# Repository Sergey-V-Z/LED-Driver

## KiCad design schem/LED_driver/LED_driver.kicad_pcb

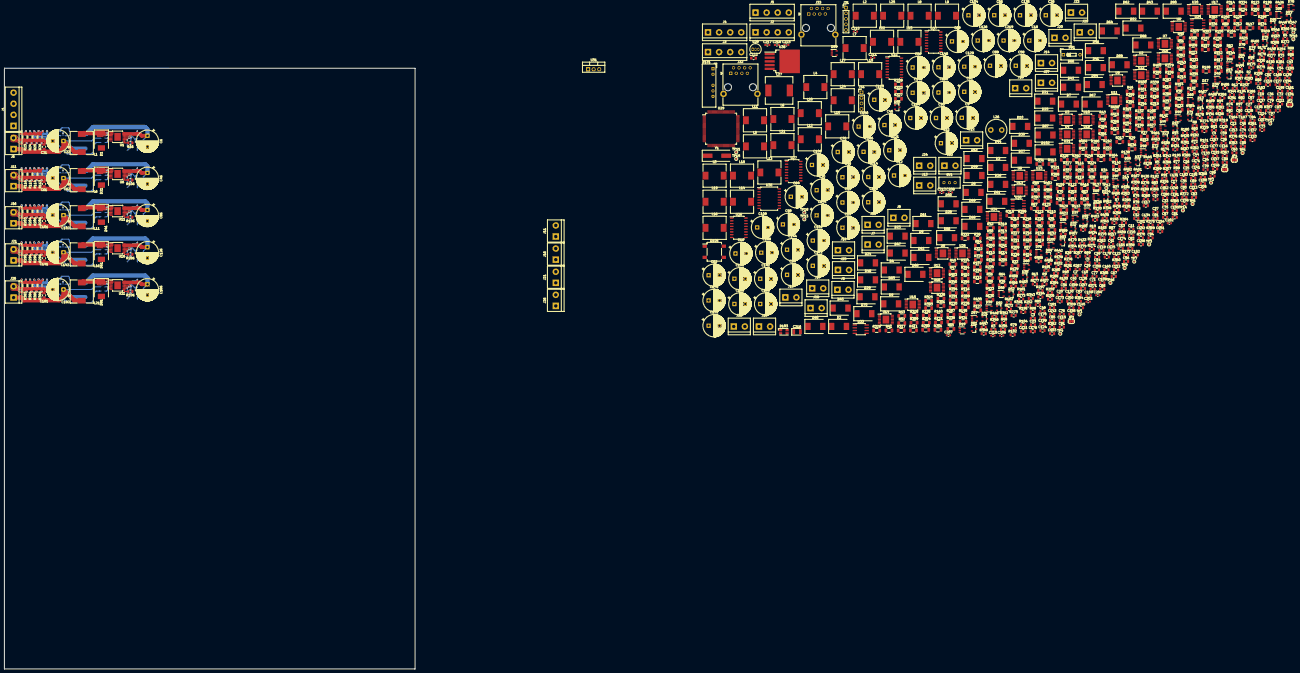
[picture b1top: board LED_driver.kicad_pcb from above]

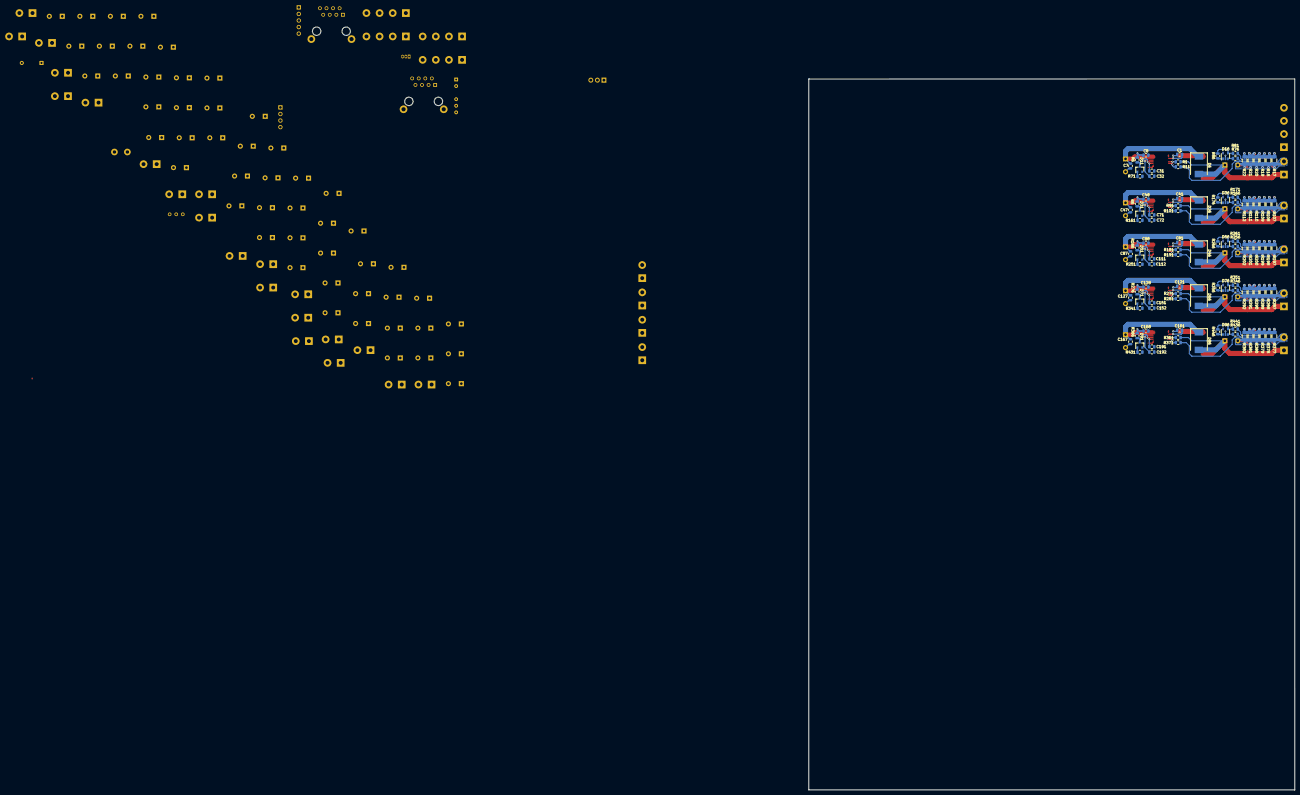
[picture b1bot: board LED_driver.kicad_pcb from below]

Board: 2 copper layers, 188.0 x 275.0 mm, 1054 parts (105 on the bottom side), 457 nets.

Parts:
C1, C2, C3, C4, C5, C7, C8, C10, C11, C13, C14, C16, C17, C19, C20, C21, C23, C25, C27, C29, C31, C33, C35, C37, C39, C41, C41#2, C42, C43, C44, C45, C47, C47#2, C48, C48#2, C50, C51, C53, C54, C56, C57, C59, C60, C61, C61#2, C63, C65, C67, C69, C71, C71#2, C73, C75, C77, C79, C81, C81#2, C82, C83, C84, C85, C87, C87#2, C88, C88#2, C90, C91, C93, C94, C96, C97, C99, C100, C101, C101#2, C103, C105, C107, C109, C111, C111#2, C113, C115, C117, C119, C121, C121#2, C122, C123, C124, C125, C127, C127#2, C128, C128#2, C130, C131, C133, C134, C136, C137, C139, C140, C141, C141#2, C143, C145, C147, C149, C151, C151#2, C153, C155, C157, C159, C161, C161#2, C162, C163, C164, C165, C167, C167#2, C168, C168#2, C170, C171, C173, C174, C176, C177, C179, C180, C181, C181#2, C183, C185, C187, C189, C191, C191#2, C193, C195, C197, C199, C201, C209, C213, C220: 0.1mkF; C_0805_2012Metric
C6, C9, C12, C15, C18, C22, C24, C26, C28, C30, C46, C46#2, C49, C52, C55, C58, C62, C62#2, C64, C66, C68, C70, C86, C86#2, C89, C92, C95, C98, C102, C102#2, C104, C106, C108, C110, C126, C126#2, C129, C132, C135, C138, C142, C142#2, C144, C146, C148, C150, C166, C166#2, C169, C172, C175, C178, C182, C182#2, C184, C186, C188, C190: 470mkF; CP_Radial_D10.0mm_P5.00mm
C32, C34, C36, C38, C40, C72, C72#2, C74, C76, C78, C80, C112, C112#2, C114, C116, C118, C120, C152, C152#2, C154, C156, C158, C160, C192, C192#2, C194, C196, C198, C200: 1mkF; C_0805_2012Metric
C202, C203, C204, C205, C206, C207, C208, C212, C215: 0.1uf; C_0603_1608Metric
C210, C211: 18pF; C_0603_1608Metric
C214: 100uf 16v; CP_Radial_D10.0mm_P5.00mm
C216: 10uf 10v; CP_EIA-3528-21_Kemet-B
C217, C218, C223: 0.1 mkf; C_0603_1608Metric_Pad1.05x0.95mm_HandSolder
C219: 220uf 50v; CP_Radial_D10.0mm_P5.00mm
C221: 470uf 50v; CP_Radial_D10.0mm_P5.00mm
C222: 10 mkf; C_0805_2012Metric_Pad1.15x1.40mm_HandSolder
D1, D2, D3, D4, D5, D6, D7, D8, D9, D10, D21, D21#2, D22, D23, D24, D25, D26, D26#2, D27, D28, D29, D30, D41, D41#2, D42, D43, D44, D45, D46, D46#2, D47, D48, D49, D50, D61, D61#2, D62, D63, D64, D65, D66, D66#2, D67, D68, D69, D70, D81, D81#2, D82, D83, D84, D85, D86, D86#2, D87, D88, D89, D90, D102: D_Schottky; D_SMC
D11, D12, D13, D14, D15, D31, D31#2, D32, D33, D34, D35, D51, D51#2, D52, D53, D54, D55, D71, D71#2, D72, D73, D74, D75, D91, D91#2, D92, D93, D94, D95: Si2300; SOT-23
D16, D17, D18, D19, D20, D36, D36#2, D37, D38, D39, D40, D56, D56#2, D57, D58, D59, D60, D76, D76#2, D77, D78, D79, D80, D96, D96#2, D97, D98, D99, D100: lmc7101; SOT-23-5
D101: AM1DS-0505S-NZ; Converter_DCDC_muRata_NMAxxxxSC_THT
D103: Led_RGB_CA_2; LED_Avago_PLCC4_3.2x2.8mm_CW
D104: SM712; SOT-23
D105: B380R; Diode_Bridge_Vishay_DFS
D106: LED; LED_0805_2012Metric
J1, J2, J3, J4, J5: Screw_Terminal_01x04; TerminalBlock_bornier-4_P5.08mm
J6, J7, J8, J9, J10, J11, J11#2, J12, J13, J14, J15, J16, J16#2, J17, J18, J19, J20, J21, J21#2, J22, J23, J24, J25, J26, J26#2, J27, J28, J29, J30, J35: Screw_Terminal_01x02; TerminalBlock_bornier-2_P5.08mm
J31: SWD; PinHeader_1x05_P2.54mm_Vertical
J32, J33: RJ45_Shielded; RJ45_Ninigi_GE
J34: DEBUG; PinHeader_1x04_P2.54mm_Vertical
JP1: TX_UA; SolderJumper-2_P1.3mm_Bridged_RoundedPad1.0x1.5mm
JP2: RX_UA; SolderJumper-2_P1.3mm_Bridged_RoundedPad1.0x1.5mm
JP3: TX_CAN; SolderJumper-2_P1.3mm_Open_RoundedPad1.0x1.5mm
JP4: RX_CAN; SolderJumper-2_P1.3mm_Open_RoundedPad1.0x1.5mm
L1, L2, L3, L4, L5, L6, L6#2, L7, L8, L9, L10, L11, L11#2, L12, L13, L14, L15, L16, L16#2, L17, L18, L19, L20, L21, L21#2, L22, L23, L24, L25: 22mkH; L_10.4x10.4_H4.8
L26: 22 uH; L_Radial_D9.5mm_P5.00mm_Fastron_07HVP
L27: 33 uH; L_12x12mm_H8mm
R1, R2, R3, R4, R5, R11, R12, R13, R14, R15, R76, R77, R78, R79, R80, R81, R82, R83, R84, R85, R91, R91#2, R92, R93, R94, R95, R101, R101#2, R102, R103, R104, R105, R166, R166#2, R167, R168, R169, R170, R171, R171#2, R172, R173, R174, R175, R181, R181#2, R182, R183, R184, R185, R191, R191#2, R192, R193, R194, R195, R256, R256#2, R257, R258, R259, R260, R261, R261#2, R262, R263, R264, R265, R271, R271#2, R272, R273, R274, R275, R281, R281#2, R282, R283, R284, R285, R346, R346#2, R347, R348, R349, R350, R351, R351#2, R352, R353, R354, R355, R361, R361#2, R362, R363, R364, R365, R371, R371#2, R372, R373, R374, R375, R436, R436#2, R437, R438, R439, R440, R441, R441#2, R442, R443, R444, R445, R455, R465: 1K; R_0805_2012Metric
R6, R6#2, R7, R8, R9, R10, R71, R72, R73, R74, R75, R96, R97, R98, R99, R100, R161, R161#2, R162, R163, R164, R165, R186, R186#2, R187, R188, R189, R190, R251, R251#2, R252, R253, R254, R255, R276, R276#2, R277, R278, R279, R280, R341, R341#2, R342, R343, R344, R345, R366, R366#2, R367, R368, R369, R370, R431, R431#2, R432, R433, R434, R435: 100K; R_0805_2012Metric
R16, R27, R38, R49, R60, R106, R106#2, R117, R128, R139, R150, R196, R196#2, R207, R218, R229, R240, R286, R286#2, R297, R308, R319, R330, R376, R376#2, R387, R398, R409, R420, R457: 100; R_0805_2012Metric
R17, R18, R19, R20, R21, R22, R23, R24, R25, R26, R28, R29, R30, R31, R32, R33, R34, R35, R36, R37, R39, R40, R41, R42, R43, R44, R45, R46, R47, R48, R50, R51, R52, R53, R54, R55, R56, R57, R58, R59, R61, R62, R63, R64, R65, R66, R67, R68, R69, R70, R107, R107#2, R108, R108#2, R109, R109#2, R110, R110#2, R111, R111#2, R112, R112#2, R113, R113#2, R114, R114#2, R115, R115#2, R116, R116#2, R118, R119, R120, R121, R122, R123, R124, R125, R126, R127, R129, R130, R131, R132, R133, R134, R135, R136, R137, R138, R140, R141, R142, R143, R144, R145, R146, R147, R148, R149, R151, R152, R153, R154, R155, R156, R157, R158, R159, R160, R197, R197#2, R198, R198#2, R199, R199#2, R200, R200#2, R201, R201#2, R202, R202#2, R203, R203#2, R204, R204#2, R205, R205#2, R206, R206#2, R208, R209, R210, R211, R212, R213, R214, R215, R216, R217, R219, R220, R221, R222, R223, R224, R225, R226, R227, R228, R230, R231, R232, R233, R234, R235, R236, R237, R238, R239, R241, R242, R243, R244, R245, R246, R247, R248, R249, R250, R287, R287#2, R288, R288#2, R289, R289#2, R290, R290#2, R291, R291#2, R292, R292#2, R293, R293#2, R294, R294#2, R295, R295#2, R296, R296#2, R298, R299, R300, R301, R302, R303, R304, R305, R306, R307, R309, R310, R311, R312, R313, R314, R315, R316, R317, R318, R320, R321, R322, R323, R324, R325, R326, R327, R328, R329, R331, R332, R333, R334, R335, R336, R337, R338, R339, R340, R377, R377#2, R378, R378#2, R379, R379#2, R380, R380#2, R381, R381#2, R382, R382#2, R383, R383#2, R384, R384#2, R385, R385#2, R386, R386#2, R388, R389, R390, R391, R392, R393, R394, R395, R396, R397, R399, R400, R401, R402, R403, R404, R405, R406, R407, R408, R410, R411, R412, R413, R414, R415, R416, R417, R418, R419, R421, R422, R423, R424, R425, R426, R427, R428, R429, R430: 1R; R_1206_3216Metric
R86, R87, R88, R89, R90, R176, R176#2, R177, R178, R179, R180, R266, R266#2, R267, R268, R269, R270, R356, R356#2, R357, R358, R359, R360, R446, R446#2, R447, R448, R449, R450, R451, R453: 10K; R_0805_2012Metric
R452: 510; R_0805_2012Metric
R454: 15; R_1206_3216Metric
R456: 3K; R_0805_2012Metric
R458, R460, R464, R469: 10k; R_0805_2012Metric_Pad1.15x1.40mm_HandSolder
R459: 120 Om; R_0805_2012Metric_Pad1.15x1.40mm_HandSolder
R461, R463: 10; R_0805_2012Metric_Pad1.15x1.40mm_HandSolder
R462: 3.3k; R_0805_2012Metric_Pad1.15x1.40mm_HandSolder
R466: 1.5k; R_0805_2012Metric_Pad1.15x1.40mm_HandSolder
R467: 1k; R_0805_2012Metric_Pad1.15x1.40mm_HandSolder
R468: 750 Om; R_0805_2012Metric_Pad1.15x1.40mm_HandSolder
RV1: 10k; Potentiometer_Bourns_3296W_Vertical
SW1: SW_DIP_x01; SW_DIP_SPSTx01_Slide_9.78x4.72mm_W7.62mm_P2.54mm
TP1: A8; TestPoint_Pad_D1.0mm
TP2: REF; TestPoint_Pad_D1.0mm
TP3: F6; TestPoint_Pad_D1.0mm
TP4: B0; TestPoint_Pad_D1.0mm
TP5: E1; TestPoint_Pad_D1.0mm
TP6: B1; TestPoint_Pad_D1.0mm
TP7: B2; TestPoint_Pad_D1.0mm
TP8: E6; TestPoint_Pad_D1.0mm
TP9: GND; TestPoint_Pad_D1.0mm
TP10: E7; TestPoint_Pad_D1.0mm
TP11: E10; TestPoint_Pad_D1.0mm
TP12: E12; TestPoint_Pad_D1.0mm
TP13: B13; TestPoint_Pad_D1.0mm
TP14: C4; TestPoint_Pad_D1.0mm
TP15: C5; TestPoint_Pad_D1.0mm
TP16: C13; TestPoint_Pad_D1.0mm
TP17: C14; TestPoint_Pad_D1.0mm
TP18: C15; TestPoint_Pad_D1.0mm
U1, U2, U3, U4, U5, U6, U6#2, U7, U8, U9, U10, U11, U11#2, U12, U13, U14, U15, U16, U16#2, U17, U18, U19, U20, U21, U21#2, U22, U23, U24, U25: LM3406; TSSOP-14-1EP_4.4x5mm_P0.65mm
U26, U27, U32, U37: 74HC595; SOP-16_4.55x10.3mm_P1.27mm
U28: TL431LP; TO-92_Inline
U29: STM32F303VCTx; LQFP-100_14x14mm_P0.5mm
U30: MCP2551-I_SN; SO-8_3.9x4.9mm_P1.27mm
U31: LM1117-3.3; TO-220-3_Vertical
U33: GD25Q16C; PowerIntegrations_SO-8
U34: MAX3485; SOIC-8_3.9x4.9mm_P1.27mm
U35: ISO7341C; SOIC-16W_7.5x10.3mm_P1.27mm
U36: LM2596S-ADJ; TO-263-5_TabPin3
Y1: Crystal_Small; Crystal_SMD_HC49-SD

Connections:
+3V3: C201.1, C202.1, C203.1, C204.1, C205.1, C206.1, C207.1, C209.1, C212.2, C213.1, C215.1, C216.1, C217.2, C220.1, D16.2, D17.2, D18.2, D19.2, D20.2, D36.2, D36#2.2, D37.2, D38.2, D39.2, D40.2, D56.2, D56#2.2, D57.2, D58.2, D59.2, D60.2, D76.2, D76#2.2, D77.2, D78.2, D79.2, D80.2, D96.2, D96#2.2, D97.2, D98.2, D99.2, D100.2, D103.4, J34.4, R451.2, R453.2, R469.1, U26.16, U27.16, U29.6, U29.22, U29.28, U29.50, U29.75, U29.100, U31.2, U32.16, U33.8, U35.1, U35.7, U37.16
/+5v_IN_ISO: C218.1, C222.1, C223.1, J32.4, J33.4, R460.2, U30.3, U34.8, U35.10, U35.16
/A_ISO: J32.2, J33.2, R459.1, R463.2
/B_ISO: J32.1, J33.1, R461.2, SW1.2
/DE: U29.71, U35.4
/DE_ISO: R464.2, U34.2, U34.3, U35.13
/DIM_CH1: R16.2, R106.2, R196.2, R286.2, R376.2, U29.84
/DIM_CH2: R106#2.2, U29.85
/DIM_CH3: R196#2.2, U29.92
/DIM_CH4: R286#2.2, U29.93
/DIM_CH5: R376#2.2, U29.95
/DIM_CH6: R27.2, U29.1
/DIM_CH7: R117.2, U29.2
/DIM_CH8: R207.2, U29.3
/DIM_CH9: R297.2, U29.4
/DIM_CH10: R387.2, U29.10
/DIM_CH11: R38.2, U29.11
/DIM_CH12: R128.2, U29.31
/DIM_CH13: R218.2, U29.32
/DIM_CH14: R308.2, U29.40
/DIM_CH15: R398.2, U29.42
/DIM_CH16: R49.2, U29.44
/DIM_CH17: R139.2, U29.47
/DIM_CH18: R229.2, U29.48
/DIM_CH19: R319.2, U29.62
/DIM_CH20: R409.2, U29.63
/DIM_CH21: R60.2, U29.64
/DIM_CH22: R150.2, U29.65
/DIM_CH23: R240.2, U29.66
/DIM_CH24: R330.2, R420.2, U29.70
/GND_5v_IN_ISO: C218.2, C222.2, C223.2, D104.3, J32.3, J32.SH, J33.3, J33.SH, R458.1, R464.1, U30.2, U34.5, U35.9, U35.15
/IN_+24v: C221.1, D105.1, J32.7, J33.7, U36.1
/IN_GND_24v: C219.2, C221.2, D101.2, D102.2, D105.3, J32.8, J33.8, R465.1, U36.3, U36.5
/Isens_CH1: D16.1, D36.1, D56.1, D76.1, D96.1, R86.2, R176.2, R266.2, R356.2, R446.2, U29.15
/Isens_CH2: D36#2.1, R176#2.2, U29.16
/Isens_CH3: D56#2.1, R266#2.2, U29.17
/Isens_CH4: D76#2.1, R356#2.2, U29.18
/Isens_CH5: D96#2.1, R446#2.2, U29.19
/Isens_CH6: D17.1, R87.2, U29.23
/Isens_CH7: D37.1, R177.2, U29.24
/Isens_CH8: D57.1, R267.2, U29.25
/Isens_CH9: D77.1, R357.2, U29.26
/Isens_CH10: D97.1, R447.2, U29.27
/Isens_CH11: D18.1, R88.2, U29.29
/Isens_CH12: D38.1, R178.2, U29.30
/Isens_CH13: D58.1, R268.2, U29.39
/Isens_CH14: D78.1, R358.2, U29.45
/Isens_CH15: D98.1, R448.2, U29.46
/Isens_CH16: D19.1, R89.2, U29.51
/Isens_CH17: D39.1, R179.2, U29.53
/Isens_CH18: D59.1, R269.2, U29.54
/Isens_CH19: D79.1, R359.2, U29.55
/Isens_CH20: D99.1, R449.2, U29.56
/Isens_CH21: D20.1, R90.2, U29.57
/Isens_CH22: D40.1, R180.2, U29.58
/Isens_CH23: D60.1, R270.2, U29.59
/Isens_CH24: D80.1, R360.2, U29.60
/Isens_CH25: D100.1, R450.2, U29.61
/LED_S1: R468.1, U37.3
/LED_S2: R467.1, U37.2
/LED_S3: R466.1, U37.1
/OFF_CH1: D11.1, D31.1, D51.1, D71.1, D91.1, R71.2, R161.2, R251.2, R341.2, R431.2, U26.15
/OFF_CH2: D31#2.1, R161#2.2, U26.1
/OFF_CH3: D51#2.1, R251#2.2, U26.2
/OFF_CH4: D71#2.1, R341#2.2, U26.3
/OFF_CH5: D91#2.1, R431#2.2, U26.4
/OFF_CH6: D12.1, R72.2, U26.5
/OFF_CH7: D32.1, R162.2, U26.6
/OFF_CH8: D52.1, R252.2, U26.7
/OFF_CH9: D72.1, R342.2, U27.15
/OFF_CH10: D92.1, R432.2, U27.1
/OFF_CH11: D13.1, R73.2, U27.2
/OFF_CH12: D33.1, R163.2, U27.3
/OFF_CH13: D53.1, R253.2, U27.4
/OFF_CH14: D73.1, R343.2, U27.5
/OFF_CH15: D93.1, R433.2, U27.6
/OFF_CH16: D14.1, R74.2, U27.7
/OFF_CH17: D34.1, R164.2, U32.15
/OFF_CH18: D54.1, R254.2, U32.1
/OFF_CH19: D74.1, R344.2, U32.2
/OFF_CH20: D94.1, R434.2, U32.3
/OFF_CH21: D15.1, R75.2, U32.4
/OFF_CH22: D35.1, R165.2, U32.5
/OFF_CH23: D55.1, R255.2, U32.6
/OFF_CH24: D75.1, R345.2, U32.7
/OFF_CH25: D95.1, R435.2, U37.15
/RESET: C208.2, J31.1, R453.1, U29.14
/RX: JP2.2, JP4.1, U35.6
/RX_ISO: R460.1, U30.4, U34.1, U35.11
/SPI3_CLK: U29.78, U33.6
/SPI3_CS: U29.83, U33.1
/SPI3_HOLD: U29.96, U33.7
/SPI3_MISO: U29.79, U33.2
/SPI3_MOSI: U29.80, U33.5
/SPI3_WP: U29.97, U33.3
/SWDCL: J31.4, U29.76
/SWDIO: J31.2, U29.72
/TX: JP1.2, JP3.1, U35.5
/TX_ISO: U30.1, U34.4, U35.12
/USART2_RX: J34.3, U29.87
/USART2_TX: J34.1, U29.86
/spi_CS: U26.12, U27.12, U29.77, U32.12, U37.12
/spi_MOSI: U26.14, U29.91
/spi_SCK: U26.11, U27.11, U29.89, U32.11, U37.11
/~MR: U26.10, U27.10, U29.90, U32.10, U37.10
/~OE: U26.13, U27.13, U29.88, U32.13, U37.13
GND: C6.2, C7.2, C8.2, C9.2, C10.2, C11.2, C12.2, C13.2, C14.2, C15.2, C16.2, C17.2, C18.2, C19.2, C20.2, C31.2, C32.2, C33.2, C34.2, C35.2, C36.2, C37.2, C38.2, C39.2, C40.2, C46.2, C46#2.2, C47.2, C47#2.2, C48.2, C48#2.2, C49.2, C50.2, C51.2, C52.2, C53.2, C54.2, C55.2, C56.2, C57.2, C58.2, C59.2, C60.2, C71.2, C71#2.2, C72.2, C72#2.2, C73.2, C74.2, C75.2, C76.2, C77.2, C78.2, C79.2, C80.2, C86.2, C86#2.2, C87.2, C87#2.2, C88.2, C88#2.2, C89.2, C90.2, C91.2, C92.2, C93.2, C94.2, C95.2, C96.2, C97.2, C98.2, C99.2, C100.2, C111.2, C111#2.2, C112.2, C112#2.2, C113.2, C114.2, C115.2, C116.2, C117.2, C118.2, C119.2, C120.2, C126.2, C126#2.2, C127.2, C127#2.2, C128.2, C128#2.2, C129.2, C130.2, C131.2, C132.2, C133.2, C134.2, C135.2, C136.2, C137.2, C138.2, C139.2, C140.2, C151.2, C151#2.2, C152.2, C152#2.2, C153.2, C154.2, C155.2, C156.2, C157.2, C158.2, C159.2, C160.2, C166.2, C166#2.2, C167.2, C167#2.2, C168.2, C168#2.2, C169.2, C170.2, C171.2, C172.2, C173.2, C174.2, C175.2, C176.2, C177.2, C178.2, C179.2, C180.2, C191.2, C191#2.2, C192.2, C192#2.2, C193.2, C194.2, C195.2, C196.2, C197.2, C198.2, C199.2, C200.2, C201.2, C202.2, C203.2, C204.2, C205.2, C206.2, C207.2, C208.1, C209.2, C210.2, C211.1, C212.1, C213.2, C214.2, C215.2, C216.2, C217.1, C220.2, D1.2, D2.2, D3.2, D4.2, D5.2, D11.2, D12.2, D13.2, D14.2, D15.2, D16.5, D17.5, D18.5, D19.5, D20.5, D21.2, D21#2.2, D22.2, D23.2, D24.2, D25.2, D31.2, D31#2.2, D32.2, D33.2, D34.2, D35.2, D36.5, D36#2.5, D37.5, D38.5, D39.5, D40.5, D41.2, D41#2.2, D42.2, D43.2, D44.2, D45.2, D51.2, D51#2.2, D52.2, D53.2, D54.2, D55.2, D56.5, D56#2.5, D57.5, D58.5, D59.5, D60.5, D61.2, D61#2.2, D62.2, D63.2, D64.2, D65.2, D71.2, D71#2.2, D72.2, D73.2, D74.2, D75.2, D76.5, D76#2.5, D77.5, D78.5, D79.5, D80.5, D81.2, D81#2.2, D82.2, D83.2, D84.2, D85.2, D91.2, D91#2.2, D92.2, D93.2, D94.2, D95.2, D96.5, D96#2.5, D97.5, D98.5, D99.5, D100.5, D101.4, D106.1, J1.1, J1.2, J2.1, J2.2, J3.1, J3.2, J4.1, J4.2, J5.1, J5.2, J31.3, J34.2, R17.1, R18.1, R19.1, R20.1, R21.1, R22.1, R23.1, R24.1, R25.1, R26.1, R28.1, R29.1, R30.1, R31.1, R32.1, R33.1, R34.1, R35.1, R36.1, R37.1, R39.1, R40.1, R41.1, R42.1, R43.1, R44.1, R45.1, R46.1, R47.1, R48.1, R50.1, R51.1, R52.1, R53.1, R54.1, R55.1, R56.1, R57.1, R58.1, R59.1, R61.1, R62.1, R63.1, R64.1, R65.1, R66.1, R67.1, R68.1, R69.1, R70.1, R71.1, R72.1, R73.1, R74.1, R75.1, R81.1, R82.1, R83.1, R84.1, R85.1, R107.1, R107#2.1, R108.1, R108#2.1, R109.1, R109#2.1, R110.1, R110#2.1, R111.1, R111#2.1, R112.1, R112#2.1, R113.1, R113#2.1, R114.1, R114#2.1, R115.1, R115#2.1, R116.1, R116#2.1, R118.1, R119.1, R120.1, R121.1, R122.1, R123.1, R124.1, R125.1, R126.1, R127.1, R129.1, R130.1, R131.1, R132.1, R133.1, R134.1, R135.1, R136.1, R137.1, R138.1, R140.1, R141.1, R142.1, R143.1, R144.1, R145.1, R146.1, R147.1, R148.1, R149.1, R151.1, R152.1, R153.1, R154.1, R155.1, R156.1, R157.1, R158.1, R159.1, R160.1, R161.1, R161#2.1, R162.1, R163.1, R164.1, R165.1, R171.1, R171#2.1, R172.1, R173.1, R174.1, R175.1, R197.1, R197#2.1, R198.1, R198#2.1, R199.1, R199#2.1, R200.1, R200#2.1, R201.1, R201#2.1, R202.1, R202#2.1, R203.1, R203#2.1, R204.1, R204#2.1, R205.1, R205#2.1, R206.1, R206#2.1, R208.1, R209.1, R210.1, R211.1, R212.1, R213.1, R214.1, R215.1, R216.1, R217.1, R219.1, R220.1, R221.1, R222.1, R223.1, R224.1, R225.1, R226.1, R227.1, R228.1, R230.1, R231.1, R232.1, R233.1, R234.1, R235.1, R236.1, R237.1, R238.1, R239.1, R241.1, R242.1, R243.1, R244.1, R245.1, R246.1, R247.1, R248.1, R249.1, R250.1, R251.1, R251#2.1, R252.1, R253.1, R254.1, R255.1, R261.1, R261#2.1, R262.1, R263.1, R264.1, R265.1, R287.1, R287#2.1, R288.1, R288#2.1, R289.1, R289#2.1, R290.1, R290#2.1, R291.1, R291#2.1, R292.1, R292#2.1, R293.1, R293#2.1, R294.1, R294#2.1, R295.1, R295#2.1, R296.1, R296#2.1, R298.1, R299.1, R300.1, R301.1, R302.1, R303.1, R304.1, R305.1, R306.1, R307.1, R309.1, R310.1, R311.1, R312.1, R313.1, R314.1, R315.1, R316.1, R317.1, R318.1, R320.1, R321.1, R322.1, R323.1, R324.1, R325.1, R326.1, R327.1, R328.1, R329.1, R331.1, R332.1, R333.1, R334.1, R335.1, R336.1, R337.1, R338.1, R339.1, R340.1, R341.1, R341#2.1, R342.1, R343.1, R344.1, R345.1, R351.1, R351#2.1, R352.1, R353.1, R354.1, R355.1, R377.1, R377#2.1, R378.1, R378#2.1, R379.1, R379#2.1, R380.1, R380#2.1, R381.1, R381#2.1, R382.1, R382#2.1, R383.1, R383#2.1, R384.1, R384#2.1, R385.1, R385#2.1, R386.1, R386#2.1, R388.1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
unnamed: C1.1, C41.1, C81.1, C121.1, C161.1, D1.1, D21.1, D41.1, D61.1, D81.1, L1.1, L6.1, L11.1, L16.1, L21.1, U1.1, U1.2, U6.1, U6.2, U11.1, U11.2, U16.1, U16.2, U21.1, U21.2
unnamed: C1.2, C41.2, C81.2, C121.2, C161.2, U1.3, U6.3, U11.3, U16.3, U21.3
unnamed: C2.1, D2.1, L2.1, U2.1, U2.2
unnamed: C2.2, U2.3
unnamed: C3.1, D3.1, L3.1, U3.1, U3.2
unnamed: C3.2, U3.3
unnamed: C4.1, D4.1, L4.1, U4.1, U4.2
unnamed: C4.2, U4.3
unnamed: C5.1, D5.1, L5.1, U5.1, U5.2
unnamed: C5.2, U5.3
unnamed: C9.1, C10.1, C11.1, C49.1, C50.1, C51.1, C89.1, C90.1, C91.1, C129.1, C130.1, C131.1, C169.1, C170.1, C171.1, D7.1, D27.1, D47.1, D67.1, D87.1, J2.3, J2.4, R7.2, R97.2, R187.2, R277.2, R367.2, U2.12, U2.13, U2.14, U7.12, U7.13, U7.14, U12.12, U12.13, U12.14, U17.12, U17.13, U17.14, U22.12, U22.13, U22.14
unnamed: C12.1, C13.1, C14.1, C52.1, C53.1, C54.1, C92.1, C93.1, C94.1, C132.1, C133.1, C134.1, C172.1, C173.1, C174.1, D8.1, D28.1, D48.1, D68.1, D88.1, J3.3, J3.4, R8.2, R98.2, R188.2, R278.2, R368.2, U3.12, U3.13, U3.14, U8.12, U8.13, U8.14, U13.12, U13.13, U13.14, U18.12, U18.13, U18.14, U23.12, U23.13, U23.14
unnamed: C21.1, C22.1, C61.1, C62.1, C101.1, C102.1, C141.1, C142.1, C181.1, C182.1, D6.2, D26.2, D46.2, D66.2, D86.2, J6.1, J11.1, J16.1, J21.1, J26.1, L1.2, L6.2, L11.2, L16.2, L21.2, R1.1, R91.1, R181.1, R271.1, R361.1
unnamed: C21.2, C22.2, C61.2, C62.2, C101.2, C102.2, C141.2, C142.2, C181.2, C182.2, J6.2, J11.2, J16.2, J21.2, J26.2, R11.1, R17.2, R18.2, R19.2, R20.2, R21.2, R22.2, R23.2, R24.2, R25.2, R26.2, R76.1, R101.1, R107.2, R108.2, R109.2, R110.2, R111.2, R112.2, R113.2, R114.2, R115.2, R116.2, R166.1, R191.1, R197.2, R198.2, R199.2, R200.2, R201.2, R202.2, R203.2, R204.2, R205.2, R206.2, R256.1, R281.1, R287.2, R288.2, R289.2, R290.2, R291.2, R292.2, R293.2, R294.2, R295.2, R296.2, R346.1, R371.1, R377.2, R378.2, R379.2, R380.2, R381.2, R382.2, R383.2, R384.2, R385.2, R386.2, R436.1
unnamed: C23.1, C24.1, D7.2, J7.1, L2.2, R2.1
unnamed: C23.2, C24.2, J7.2, R12.1, R28.2, R29.2, R30.2, R31.2, R32.2, R33.2, R34.2, R35.2, R36.2, R37.2, R77.1
unnamed: C25.1, C26.1, D8.2, J8.1, L3.2, R3.1
unnamed: C25.2, C26.2, J8.2, R13.1, R39.2, R40.2, R41.2, R42.2, R43.2, R44.2, R45.2, R46.2, R47.2, R48.2, R78.1
unnamed: C27.1, C28.1, D9.2, J9.1, L4.2, R4.1
unnamed: C27.2, C28.2, J9.2, R14.1, R50.2, R51.2, R52.2, R53.2, R54.2, R55.2, R56.2, R57.2, R58.2, R59.2, R79.1
unnamed: C29.1, C30.1, D10.2, J10.1, L5.2, R5.1
unnamed: C29.2, C30.2, J10.2, R15.1, R61.2, R62.2, R63.2, R64.2, R65.2, R66.2, R67.2, R68.2, R69.2, R70.2, R80.1
unnamed: C31.1, C71.1, C111.1, C151.1, C191.1, U1.9, U6.9, U11.9, U16.9, U21.9
unnamed: C32.1, C72.1, C112.1, C152.1, C192.1, U1.11, U6.11, U11.11, U16.11, U21.11
unnamed: C33.1, U2.9
unnamed: C34.1, U2.11
unnamed: C35.1, U3.9
unnamed: C36.1, U3.11
unnamed: C37.1, U4.9
unnamed: C38.1, U4.11
unnamed: C39.1, U5.9
unnamed: C40.1, U5.11
unnamed: C41#2.1, D21#2.1, L6#2.1, U6#2.1, U6#2.2
unnamed: C41#2.2, U6#2.3
unnamed: C42.1, D22.1, L7.1, U7.1, U7.2
unnamed: C42.2, U7.3
unnamed: C43.1, D23.1, L8.1, U8.1, U8.2
unnamed: C43.2, U8.3
unnamed: C44.1, D24.1, L9.1, U9.1, U9.2
unnamed: C44.2, U9.3
unnamed: C45.1, D25.1, L10.1, U10.1, U10.2
unnamed: C45.2, U10.3
unnamed: C61#2.1, C62#2.1, D26#2.2, J11#2.1, L6#2.2, R91#2.1
unnamed: C61#2.2, C62#2.2, J11#2.2, R101#2.1, R107#2.2, R108#2.2, R109#2.2, R110#2.2, R111#2.2, R112#2.2, R113#2.2, R114#2.2, R115#2.2, R116#2.2, R166#2.1
unnamed: C63.1, C64.1, D27.2, J12.1, L7.2, R92.1
unnamed: C63.2, C64.2, J12.2, R102.1, R118.2, R119.2, R120.2, R121.2, R122.2, R123.2, R124.2, R125.2, R126.2, R127.2, R167.1
unnamed: C65.1, C66.1, D28.2, J13.1, L8.2, R93.1
unnamed: C65.2, C66.2, J13.2, R103.1, R129.2, R130.2, R131.2, R132.2, R133.2, R134.2, R135.2, R136.2, R137.2, R138.2, R168.1
unnamed: C67.1, C68.1, D29.2, J14.1, L9.2, R94.1
unnamed: C67.2, C68.2, J14.2, R104.1, R140.2, R141.2, R142.2, R143.2, R144.2, R145.2, R146.2, R147.2, R148.2, R149.2, R169.1
unnamed: C69.1, C70.1, D30.2, J15.1, L10.2, R95.1
unnamed: C69.2, C70.2, J15.2, R105.1, R151.2, R152.2, R153.2, R154.2, R155.2, R156.2, R157.2, R158.2, R159.2, R160.2, R170.1
unnamed: C71#2.1, U6#2.9
unnamed: C72#2.1, U6#2.11
unnamed: C73.1, U7.9
unnamed: C74.1, U7.11
unnamed: C75.1, U8.9
unnamed: C76.1, U8.11
unnamed: C77.1, U9.9
unnamed: C78.1, U9.11
unnamed: C79.1, U10.9
unnamed: C80.1, U10.11
unnamed: C81#2.1, D41#2.1, L11#2.1, U11#2.1, U11#2.2
unnamed: C81#2.2, U11#2.3
unnamed: C82.1, D42.1, L12.1, U12.1, U12.2
unnamed: C82.2, U12.3
unnamed: C83.1, D43.1, L13.1, U13.1, U13.2
unnamed: C83.2, U13.3
unnamed: C84.1, D44.1, L14.1, U14.1, U14.2
unnamed: C84.2, U14.3
unnamed: C85.1, D45.1, L15.1, U15.1, U15.2
unnamed: C85.2, U15.3
unnamed: C18.1, C19.1, C20.1, C58.1, C59.1, C60.1, C98.1, C99.1, C100.1, C138.1, C139.1, C140.1, C178.1, C179.1, C180.1, D10.1, D30.1, D50.1, D70.1, D90.1, J5.3, J5.4, R10.2, R100.2, R190.2, R280.2, R370.2, U5.12, U5.13, U5.14, U10.12, U10.13, U10.14, U15.12, U15.13, U15.14, U20.12, U20.13, U20.14, U25.12, U25.13, U25.14
unnamed: C101#2.1, C102#2.1, D46#2.2, J16#2.1, L11#2.2, R181#2.1
unnamed: C101#2.2, C102#2.2, J16#2.2, R191#2.1, R197#2.2, R198#2.2, R199#2.2, R200#2.2, R201#2.2, R202#2.2, R203#2.2, R204#2.2, R205#2.2, R206#2.2, R256#2.1
unnamed: C103.1, C104.1, D47.2, J17.1, L12.2, R182.1
unnamed: C103.2, C104.2, J17.2, R192.1, R208.2, R209.2, R210.2, R211.2, R212.2, R213.2, R214.2, R215.2, R216.2, R217.2, R257.1
unnamed: C105.1, C106.1, D48.2, J18.1, L13.2, R183.1
unnamed: C105.2, C106.2, J18.2, R193.1, R219.2, R220.2, R221.2, R222.2, R223.2, R224.2, R225.2, R226.2, R227.2, R228.2, R258.1
unnamed: C107.1, C108.1, D49.2, J19.1, L14.2, R184.1
unnamed: C107.2, C108.2, J19.2, R194.1, R230.2, R231.2, R232.2, R233.2, R234.2, R235.2, R236.2, R237.2, R238.2, R239.2, R259.1
unnamed: C109.1, C110.1, D50.2, J20.1, L15.2, R185.1
unnamed: C109.2, C110.2, J20.2, R195.1, R241.2, R242.2, R243.2, R244.2, R245.2, R246.2, R247.2, R248.2, R249.2, R250.2, R260.1
unnamed: C111#2.1, U11#2.9
unnamed: C112#2.1, U11#2.11
unnamed: C113.1, U12.9
unnamed: C114.1, U12.11
unnamed: C115.1, U13.9
unnamed: C116.1, U13.11
unnamed: C117.1, U14.9
unnamed: C118.1, U14.11
unnamed: C119.1, U15.9
unnamed: C120.1, U15.11
unnamed: C121#2.1, D61#2.1, L16#2.1, U16#2.1, U16#2.2
unnamed: C121#2.2, U16#2.3
unnamed: C122.1, D62.1, L17.1, U17.1, U17.2
unnamed: C122.2, U17.3
unnamed: C123.1, D63.1, L18.1, U18.1, U18.2
unnamed: C123.2, U18.3
unnamed: C124.1, D64.1, L19.1, U19.1, U19.2
unnamed: C124.2, U19.3
unnamed: C125.1, D65.1, L20.1, U20.1, U20.2
unnamed: C125.2, U20.3
unnamed: C6.1, C7.1, C8.1, C46.1, C46#2.1, C47.1, C47#2.1, C48.1, C48#2.1, C86.1, C86#2.1, C87.1, C87#2.1, C88.1, C88#2.1, C126.1, C126#2.1, C127.1, C127#2.1, C128.1, C128#2.1, C166.1, C166#2.1, C167.1, C167#2.1, C168.1, C168#2.1, D6.1, D26.1, D26#2.1, D46.1, D46#2.1, D66.1, D66#2.1, D86.1, D86#2.1, J1.3, J1.4, R6.2, R6#2.2, R96.2, R186.2, R186#2.2, R276.2, R276#2.2, R366.2, R366#2.2, U1.12, U1.13, U1.14, U6.12, U6.13, U6.14, U6#2.12, U6#2.13, U6#2.14, U11.12, U11.13, U11.14, U11#2.12, U11#2.13, U11#2.14, U16.12, U16.13, U16.14, U16#2.12, U16#2.13, U16#2.14, U21.12, U21.13, U21.14, U21#2.12, U21#2.13, U21#2.14
unnamed: C15.1, C16.1, C17.1, C55.1, C56.1, C57.1, C95.1, C96.1, C97.1, C135.1, C136.1, C137.1, C175.1, C176.1, C177.1, D9.1, D29.1, D49.1, D69.1, D89.1, J4.3, J4.4, R9.2, R99.2, R189.2, R279.2, R369.2, U4.12, U4.13, U4.14, U9.12, U9.13, U9.14, U14.12, U14.13, U14.14, U19.12, U19.13, U19.14, U24.12, U24.13, U24.14
unnamed: C141#2.1, C142#2.1, D66#2.2, J21#2.1, L16#2.2, R271#2.1
unnamed: C141#2.2, C142#2.2, J21#2.2, R281#2.1, R287#2.2, R288#2.2, R289#2.2, R290#2.2, R291#2.2, R292#2.2, R293#2.2, R294#2.2, R295#2.2, R296#2.2, R346#2.1
unnamed: C143.1, C144.1, D67.2, J22.1, L17.2, R272.1
unnamed: C143.2, C144.2, J22.2, R282.1, R298.2, R299.2, R300.2, R301.2, R302.2, R303.2, R304.2, R305.2, R306.2, R307.2, R347.1
unnamed: C145.1, C146.1, D68.2, J23.1, L18.2, R273.1
unnamed: C145.2, C146.2, J23.2, R283.1, R309.2, R310.2, R311.2, R312.2, R313.2, R314.2, R315.2, R316.2, R317.2, R318.2, R348.1
unnamed: C147.1, C148.1, D69.2, J24.1, L19.2, R274.1
unnamed: C147.2, C148.2, J24.2, R284.1, R320.2, R321.2, R322.2, R323.2, R324.2, R325.2, R326.2, R327.2, R328.2, R329.2, R349.1
unnamed: C149.1, C150.1, D70.2, J25.1, L20.2, R275.1
unnamed: C149.2, C150.2, J25.2, R285.1, R331.2, R332.2, R333.2, R334.2, R335.2, R336.2, R337.2, R338.2, R339.2, R340.2, R350.1
unnamed: C151#2.1, U16#2.9
unnamed: C152#2.1, U16#2.11
unnamed: C153.1, U17.9
unnamed: C154.1, U17.11
unnamed: C155.1, U18.9
unnamed: C156.1, U18.11
unnamed: C157.1, U19.9
unnamed: C158.1, U19.11
unnamed: C159.1, U20.9
unnamed: C160.1, U20.11
unnamed: C161#2.1, D81#2.1, L21#2.1, U21#2.1, U21#2.2
unnamed: C161#2.2, U21#2.3
unnamed: C162.1, D82.1, L22.1, U22.1, U22.2
unnamed: C162.2, U22.3
unnamed: C163.1, D83.1, L23.1, U23.1, U23.2
unnamed: C163.2, U23.3
unnamed: C164.1, D84.1, L24.1, U24.1, U24.2
unnamed: C164.2, U24.3
unnamed: C165.1, D85.1, L25.1, U25.1, U25.2
unnamed: C165.2, U25.3
unnamed: C181#2.1, C182#2.1, D86#2.2, J26#2.1, L21#2.2, R361#2.1
unnamed: C181#2.2, C182#2.2, J26#2.2, R371#2.1, R377#2.2, R378#2.2, R379#2.2, R380#2.2, R381#2.2, R382#2.2, R383#2.2, R384#2.2, R385#2.2, R386#2.2, R436#2.1
unnamed: C183.1, C184.1, D87.2, J27.1, L22.2, R362.1
unnamed: C183.2, C184.2, J27.2, R372.1, R388.2, R389.2, R390.2, R391.2, R392.2, R393.2, R394.2, R395.2, R396.2, R397.2, R437.1
unnamed: C185.1, C186.1, D88.2, J28.1, L23.2, R363.1
unnamed: C185.2, C186.2, J28.2, R373.1, R399.2, R400.2, R401.2, R402.2, R403.2, R404.2, R405.2, R406.2, R407.2, R408.2, R438.1
unnamed: C187.1, C188.1, D89.2, J29.1, L24.2, R364.1
unnamed: C187.2, C188.2, J29.2, R374.1, R410.2, R411.2, R412.2, R413.2, R414.2, R415.2, R416.2, R417.2, R418.2, R419.2, R439.1
unnamed: C189.1, C190.1, D90.2, J30.1, L25.2, R365.1
unnamed: C189.2, C190.2, J30.2, R375.1, R421.2, R422.2, R423.2, R424.2, R425.2, R426.2, R427.2, R428.2, R429.2, R430.2, R440.1
unnamed: C191#2.1, U21#2.9
unnamed: C192#2.1, U21#2.11
unnamed: C193.1, U22.9
unnamed: C194.1, U22.11
unnamed: C195.1, U23.9
unnamed: C196.1, U23.11
unnamed: C197.1, U24.9
unnamed: C198.1, U24.11
unnamed: C199.1, U25.9
unnamed: C200.1, U25.11
unnamed: C210.1, U29.12, Y1.1
unnamed: C211.2, U29.13, Y1.2
unnamed: C214.1, L26.2, R454.2, U31.3
unnamed: C219.1, D101.1, L27.2, R462.2
unnamed: D11.3, D31.3, D51.3, D71.3, D91.3, R6.1, R6#2.1, R186.1, R276.1, R366.1, U1.10, U6.10, U11.10, U16.10, U21.10
unnamed: D12.3, R7.1, U2.10
unnamed: D13.3, R8.1, U3.10
unnamed: D14.3, R9.1, U4.10
unnamed: D15.3, R10.1, U5.10
unnamed: D16.3, D36.3, D56.3, D76.3, D96.3, R76.2, R166.2, R256.2, R346.2, R436.2
unnamed: D16.4, D36.4, D56.4, D76.4, D96.4, R81.2, R86.1, R171.2, R176.1, R261.2, R266.1, R351.2, R356.1, R441.2, R446.1
unnamed: D17.3, R77.2
unnamed: D17.4, R82.2, R87.1
unnamed: D18.3, R78.2
unnamed: D18.4, R83.2, R88.1
unnamed: D19.3, R79.2
unnamed: D19.4, R84.2, R89.1
unnamed: D20.3, R80.2
unnamed: D20.4, R85.2, R90.1
unnamed: D31#2.3, R96.1, U6#2.10
unnamed: D32.3, R97.1, U7.10
unnamed: D33.3, R98.1, U8.10
unnamed: D34.3, R99.1, U9.10
unnamed: D35.3, R100.1, U10.10
unnamed: D36#2.3, R166#2.2
unnamed: D36#2.4, R171#2.2, R176#2.1
unnamed: D37.3, R167.2
unnamed: D37.4, R172.2, R177.1
unnamed: D38.3, R168.2
unnamed: D38.4, R173.2, R178.1
unnamed: D39.3, R169.2
unnamed: D39.4, R174.2, R179.1
unnamed: D40.3, R170.2
unnamed: D40.4, R175.2, R180.1
unnamed: D51#2.3, R186#2.1, U11#2.10
unnamed: D52.3, R187.1, U12.10
unnamed: D53.3, R188.1, U13.10
unnamed: D54.3, R189.1, U14.10
unnamed: D55.3, R190.1, U15.10
unnamed: D56#2.3, R256#2.2
unnamed: D56#2.4, R261#2.2, R266#2.1
unnamed: D57.3, R257.2
unnamed: D57.4, R262.2, R267.1
unnamed: D58.3, R258.2
unnamed: D58.4, R263.2, R268.1
unnamed: D59.3, R259.2
unnamed: D59.4, R264.2, R269.1
unnamed: D60.3, R260.2
unnamed: D60.4, R265.2, R270.1
unnamed: D71#2.3, R276#2.1, U16#2.10
unnamed: D72.3, R277.1, U17.10
unnamed: D73.3, R278.1, U18.10
unnamed: D74.3, R279.1, U19.10
unnamed: D75.3, R280.1, U20.10
unnamed: D76#2.3, R346#2.2
unnamed: D76#2.4, R351#2.2, R356#2.1
unnamed: D77.3, R347.2
unnamed: D77.4, R352.2, R357.1
unnamed: D78.3, R348.2
unnamed: D78.4, R353.2, R358.1
unnamed: D79.3, R349.2
unnamed: D79.4, R354.2, R359.1
unnamed: D80.3, R350.2
unnamed: D80.4, R355.2, R360.1
unnamed: D91#2.3, R366#2.1, U21#2.10
unnamed: D92.3, R367.1, U22.10
unnamed: D93.3, R368.1, U23.10
unnamed: D94.3, R369.1, U24.10
unnamed: D95.3, R370.1, U25.10
unnamed: D96#2.3, R436#2.2
unnamed: D96#2.4, R441#2.2, R446#2.1
unnamed: D97.3, R437.2
unnamed: D97.4, R442.2, R447.1
unnamed: D98.3, R438.2
unnamed: D98.4, R443.2, R448.1
unnamed: D99.3, R439.2
unnamed: D99.4, R444.2, R449.1
unnamed: D100.3, R440.2
unnamed: D100.4, R445.2, R450.1
unnamed: D101.6, L26.1
unnamed: D102.1, L27.1, U36.2
unnamed: D103.1, R466.2
unnamed: D103.2, R467.2
unnamed: D103.3, R468.2
unnamed: D104.1, R463.1, U30.6, U34.6
unnamed: D104.2, R461.1, U30.7, U34.7
unnamed: D105.2, J35.1
unnamed: D105.4, J35.2
unnamed: D106.2, R469.2
unnamed: JP1.1, U29.68
unnamed: JP2.1, U29.69
unnamed: JP3.2, U29.81
unnamed: JP4.2, U29.82
unnamed: R1.2, R91.2, R181.2, R271.2, R361.2, U1.5, U6.5, U11.5, U16.5, U21.5
unnamed: R2.2, U2.5
unnamed: R3.2, U3.5
unnamed: R4.2, U4.5
unnamed: R5.2, U5.5
unnamed: R11.2, R101.2, R191.2, R281.2, R371.2, U1.6, U6.6, U11.6, U16.6, U21.6
unnamed: R12.2, U2.6
unnamed: R13.2, U3.6
unnamed: R14.2, U4.6
unnamed: R15.2, U5.6
unnamed: R16.1, R106.1, R196.1, R286.1, R376.1, U1.8, U6.8, U11.8, U16.8, U21.8
unnamed: R27.1, U2.8
unnamed: R38.1, U3.8
unnamed: R49.1, U4.8
unnamed: R60.1, U5.8
unnamed: R91#2.2, U6#2.5
unnamed: R92.2, U7.5
unnamed: R93.2, U8.5
unnamed: R94.2, U9.5
unnamed: R95.2, U10.5
unnamed: R101#2.2, U6#2.6
unnamed: R102.2, U7.6
unnamed: R103.2, U8.6
unnamed: R104.2, U9.6
unnamed: R105.2, U10.6
unnamed: R106#2.1, U6#2.8
unnamed: R117.1, U7.8
unnamed: R128.1, U8.8
unnamed: R139.1, U9.8
unnamed: R150.1, U10.8
unnamed: R181#2.2, U11#2.5
unnamed: R182.2, U12.5
unnamed: R183.2, U13.5
unnamed: R184.2, U14.5
unnamed: R185.2, U15.5
unnamed: R191#2.2, U11#2.6
unnamed: R192.2, U12.6
unnamed: R193.2, U13.6
unnamed: R194.2, U14.6
unnamed: R195.2, U15.6
unnamed: R196#2.1, U11#2.8
unnamed: R207.1, U12.8
unnamed: R218.1, U13.8
unnamed: R229.1, U14.8
unnamed: R240.1, U15.8
unnamed: R271#2.2, U16#2.5
unnamed: R272.2, U17.5
unnamed: R273.2, U18.5
unnamed: R274.2, U19.5
unnamed: R275.2, U20.5
unnamed: R281#2.2, U16#2.6
unnamed: R282.2, U17.6
unnamed: R283.2, U18.6
unnamed: R284.2, U19.6
unnamed: R285.2, U20.6
unnamed: R286#2.1, U16#2.8
unnamed: R297.1, U17.8
unnamed: R308.1, U18.8
unnamed: R319.1, U19.8
unnamed: R330.1, U20.8
unnamed: R361#2.2, U21#2.5
unnamed: R362.2, U22.5
unnamed: R363.2, U23.5
unnamed: R364.2, U24.5
unnamed: R365.2, U25.5
unnamed: R371#2.2, U21#2.6
unnamed: R372.2, U22.6
unnamed: R373.2, U23.6
unnamed: R374.2, U24.6
unnamed: R375.2, U25.6
unnamed: R376#2.1, U21#2.8
unnamed: R387.1, U22.8
unnamed: R398.1, U23.8
unnamed: R409.1, U24.8
unnamed: R420.1, U25.8
unnamed: R451.1, R452.1, U29.94
unnamed: R454.1, R455.2, TP2.1, U28.3, U29.21
unnamed: R455.1, R456.2, RV1.1, RV1.2, U28.1
unnamed: R456.1, R457.2
unnamed: R458.2, U30.8
unnamed: R459.2, SW1.1
unnamed: R462.1, R465.2, U36.4
unnamed: TP1.1, U29.67
unnamed: TP3.1, U29.73
unnamed: TP4.1, U29.35
unnamed: TP5.1, U29.98
unnamed: TP6.1, U29.36
unnamed: TP7.1, U29.37
unnamed: TP8.1, U29.5
unnamed: TP10.1, U29.38
unnamed: TP11.1, U29.41
unnamed: TP12.1, U29.43
unnamed: TP13.1, U29.52
unnamed: TP14.1, U29.33
unnamed: TP15.1, U29.34
unnamed: TP16.1, U29.7
unnamed: TP17.1, U29.8
unnamed: TP18.1, U29.9
unnamed: U1.4, U6.4, U11.4, U16.4, U21.4
unnamed: U26.9, U27.14
unnamed: U27.9, U32.14
unnamed: U32.9, U37.14

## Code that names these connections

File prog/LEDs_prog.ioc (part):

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Mcu.Name=STM32F303V(B-C)Tx
Mcu.Package=LQFP100
Mcu.UserName=STM32F303VCTx
PA0.GPIOParameters=GPIO_Label
PA0.GPIO_Label=Isens_CH6
PA0.Mode=IN1-Single-Ended
PA0.Signal=ADC1_IN1
PA1.GPIOParameters=GPIO_Label
PA1.GPIO_Label=Isens_CH7
PA1.Mode=IN2-Single-Ended
PA1.Signal=ADC1_IN2
PA10.Mode=Asynchronous
PA10.Signal=USART1_RX
PA11.GPIOParameters=GPIO_Label
PA11.GPIO_Label=DIM_CH24
PA11.Signal=S_TIM1_CH4
PA12.Mode=Hardware Flow Control (RS485)
PA12.Signal=USART1_DE
PA13.Mode=Serial_Wire
PA13.Signal=SYS_JTMS-SWDIO
PA14.Mode=Serial_Wire
PA14.Signal=SYS_JTCK-SWCLK
PA15.Mode=NSS_Signal_Hard_Output
PA15.Signal=SPI1_NSS
PA2.GPIOParameters=GPIO_Label
PA2.GPIO_Label=Isens_CH8
PA2.Mode=IN3-Single-Ended
PA2.Signal=ADC1_IN3
PA3.GPIOParameters=GPIO_Label
PA3.GPIO_Label=Isens_CH9
PA3.Mode=IN4-Single-Ended
PA3.Signal=ADC1_IN4
PA4.GPIOParameters=GPIO_Label
PA4.GPIO_Label=Isens_CH11
PA4.Mode=IN1-Single-Ended
PA4.Signal=ADC2_IN1
PA5.GPIOParameters=GPIO_Label
PA5.GPIO_Label=Isens_CH12
PA5.Mode=IN2-Single-Ended
PA5.Signal=ADC2_IN2
PA6.GPIOParameters=GPIO_Label
PA6.GPIO_Label=DIM_CH12
PA6.Signal=S_TIM16_CH1
PA7.GPIOParameters=GPIO_Label
PA7.GPIO_Label=DIM_CH13
PA7.Signal=S_TIM17_CH1
PA9.Mode=Asynchronous
PA9.Signal=USART1_TX
PB10.GPIOParameters=GPIO_Label
PB10.GPIO_Label=DIM_CH17
PB10.Signal=S_TIM2_CH3
PB11.GPIOParameters=GPIO_Label
PB11.GPIO_Label=DIM_CH18
PB11.Signal=S_TIM2_CH4
PB12.GPIOParameters=GPIO_Label
PB12.GPIO_Label=Isens_CH16
PB12.Mode=IN3-Single-Ended
PB12.Signal=ADC4_IN3
PB14.GPIOParameters=GPIO_Label
PB14.GPIO_Label=Isens_CH17
PB14.Mode=IN4-Single-Ended
PB14.Signal=ADC4_IN4
PB15.GPIOParameters=GPIO_Label
PB15.GPIO_Label=Isens_CH18
PB15.Mode=IN5-Single-Ended
PB15.Signal=ADC4_IN5
PB3.Mode=TX_Only_Simplex_Unidirect_Master
PB3.Signal=SPI1_SCK
PB4.GPIOParameters=GPIO_Label
PB4.GPIO_Label=MR
PB4.Signal=GPIO_Output
PB5.Mode=TX_Only_Simplex_Unidirect_Master
PB5.Signal=SPI1_MOSI
PB6.GPIOParameters=GPIO_Label
PB6.GPIO_Label=DIM_CH3
PB6.Signal=S_TIM4_CH1
PB7.GPIOParameters=GPIO_Label
PB7.GPIO_Label=DIM_CH4
PB7.Signal=S_TIM4_CH2
PB8.GPIOParameters=GPIO_Label
PB8.GPIO_Label=DIM_CH5
PB8.Signal=S_TIM4_CH3
PB9.GPIOParameters=GPIO_Label
PB9.GPIO_Label=SPI3_HOLD
PB9.Signal=GPIO_Output
PC0.GPIOParameters=GPIO_Label
PC0.GPIO_Label=Isens_CH1
PC0.Signal=ADCx_IN6
PC1.GPIOParameters=GPIO_Label
PC1.GPIO_Label=Isens_CH2
PC1.Signal=ADCx_IN7
PC10.Mode=Full_Duplex_Master
PC10.Signal=SPI3_SCK
PC11.Mode=Full_Duplex_Master
PC11.Signal=SPI3_MISO
PC12.Mode=Full_Duplex_Master
PC12.Signal=SPI3_MOSI
PC2.GPIOParameters=GPIO_Label
PC2.GPIO_Label=Isens_CH3
PC2.Signal=ADCx_IN8
PC3.GPIOParameters=GPIO_Label
PC3.GPIO_Label=Isens_CH4
PC3.Signal=ADCx_IN9
PC6.GPIOParameters=GPIO_Label
PC6.GPIO_Label=DIM_CH20
PC6.Signal=S_TIM8_CH1
PC7.GPIOParameters=GPIO_Label
PC7.GPIO_Label=DIM_CH21
PC7.Signal=S_TIM8_CH2
PC8.GPIOParameters=GPIO_Label
PC8.GPIO_Label=DIM_CH22
PC8.Signal=S_TIM8_CH3
PC9.GPIOParameters=GPIO_Label
PC9.GPIO_Label=DIM_CH23
PC9.Signal=S_TIM8_CH4
PD0.Mode=Master
PD0.Signal=CAN_RX
PD1.Mode=Master
PD1.Signal=CAN_TX
PD10.GPIOParameters=GPIO_Label
PD10.GPIO_Label=Isens_CH21
PD10.Signal=ADCx_IN7P
PD11.GPIOParameters=GPIO_Label
PD11.GPIO_Label=Isens_CH22
PD11.Signal=ADCx_IN8P
PD12.GPIOParameters=GPIO_Label
PD12.GPIO_Label=Isens_CH23
PD12.Signal=ADCx_IN9P
PD13.GPIOParameters=GPIO_Label
PD13.GPIO_Label=Isens_CH24
PD13.Signal=ADCx_IN10P
PD14.GPIOParameters=GPIO_Label
PD14.GPIO_Label=Isens_CH25
PD14.Signal=ADCx_IN11
PD15.GPIOParameters=GPIO_Label
PD15.GPIO_Label=DIM_CH19
PD15.Signal=S_TIM4_CH4
PD2.GPIOParameters=GPIO_Label
PD2.GPIO_Label=SPI3_CS
PD2.Signal=GPIO_Output
PD3.GPIOParameters=GPIO_Label
PD3.GPIO_Label=DIM_CH1
PD3.Signal=S_TIM2_CH1_ETR
PD4.GPIOParameters=GPIO_Label
PD4.GPIO_Label=DIM_CH2
PD4.Signal=S_TIM2_CH2
PD5.Mode=Asynchronous
PD5.Signal=USART2_TX
PD6.Mode=Asynchronous
PD6.Signal=USART2_RX
PD7.GPIOParameters=GPIO_Label
PD7.GPIO_Label=OE
PD7.Signal=GPIO_Output
PD8.GPIOParameters=GPIO_Label
PD8.GPIO_Label=Isens_CH19
PD8.Mode=IN12-Single-Ended
PD8.Signal=ADC4_IN12
PD9.GPIOParameters=GPIO_Label
PD9.GPIO_Label=Isens_CH20
PD9.Mode=IN13-Single-Ended
PD9.Signal=ADC4_IN13
PE0.GPIOParameters=GPIO_Label
PE0.GPIO_Label=SPI3_WP
PE0.Signal=GPIO_Output
PE11.GPIOParameters=GPIO_Label
PE11.GPIO_Label=DIM_CH15
PE11.Signal=S_TIM1_CH2
PE13.GPIOParameters=GPIO_Label
PE13.GPIO_Label=DIM_CH16
PE13.Signal=S_TIM1_CH3
PE14.GPIOParameters=GPIO_Label
PE14.GPIO_Label=Isens_CH14
PE14.Mode=IN1-Single-Ended
PE14.Signal=ADC4_IN1
PE15.GPIOParameters=GPIO_Label
PE15.GPIO_Label=Isens_CH15
PE15.Mode=IN2-Single-Ended
PE15.Signal=ADC4_IN2
PE2.GPIOParameters=GPIO_Label
PE2.GPIO_Label=DIM_CH6
PE2.Signal=S_TIM3_CH1
PE3.GPIOParameters=GPIO_Label
PE3.GPIO_Label=DIM_CH7
PE3.Signal=S_TIM3_CH2
PE4.GPIOParameters=GPIO_Label
PE4.GPIO_Label=DIM_CH8
PE4.Signal=S_TIM3_CH3
PE5.GPIOParameters=GPIO_Label
PE5.GPIO_Label=DIM_CH9
PE5.Signal=S_TIM3_CH4
PE8.GPIOParameters=GPIO_Label
PE8.GPIO_Label=Isens_CH13
PE8.Signal=ADCx_IN6P
PE9.GPIOParameters=GPIO_Label
PE9.GPIO_Label=DIM_CH14
PE9.Signal=S_TIM1_CH1
PF0-OSC_IN.Mode=HSE-External-Oscillator
PF0-OSC_IN.Signal=RCC_OSC_IN
PF1-OSC_OUT.Mode=HSE-External-Oscillator
PF1-OSC_OUT.Signal=RCC_OSC_OUT
PF10.GPIOParameters=GPIO_Label
PF10.GPIO_Label=DIM_CH11
PF10.Signal=S_TIM15_CH2
PF2.GPIOParameters=GPIO_Label
PF2.GPIO_Label=Isens_CH5
PF2.Signal=ADCx_IN10
PF4.GPIOParameters=GPIO_Label
PF4.GPIO_Label=Isens_CH10
PF4.Mode=IN5-Single-Ended
PF4.Signal=ADC1_IN5
PF9.GPIOParameters=GPIO_Label
PF9.GPIO_Label=DIM_CH10
PF9.Signal=S_TIM15_CH1
RCC.HSEPLLFreq_Value=12000000
RCC.HSE_VALUE=12000000
RCC.SYSCLKFreq_VALUE=72000000
RCC.SYSCLKSourceVirtual=RCC_SYSCLKSOURCE_PLLCLK
board=custom

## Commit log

2020-07-23 Start
2020-08-04 Закончена схема
2020-08-04 Начало платы
    Начертил контур платы начал расставлять разъемы.
2020-08-05 Плата
    исправил ошибку в схеме (выключение канала). Разместил детали для одного канала (ушло времен 1 час)
2020-08-08 Плата
2020-08-08 Плата
    Закончил разводку 5 каналов
2020-08-15 Плата
    Закончил расстановку каналов и переименовывание компонентов.
2020-08-16 Плата
    Начал разводить сигналы
2020-08-17 Плата
    Закончил сигналы до каналов
2020-08-18 Плата
    Плата закончена
2021-01-25 Programming
    проект переведен в C++. Добавлен класс flash, проверен hc595
2021-01-27 Flash mod
    Добавление команд в класс spi flash
2021-01-27 ModBus add comands
    добавление команд в модбас функцию. добавлено управление выключением-включением каналов.
2021-01-27 ADC settings
2021-01-28 ADC + DMA
2021-01-28 Flash class modified
2021-01-29 Flash class end
2022-03-25 Timer setings
    Изменены настройки таймеров установлена частота 1Мгц
    Добавлены дефайны каналов шим
2022-03-28 End code for PWM
2022-03-28 uart
